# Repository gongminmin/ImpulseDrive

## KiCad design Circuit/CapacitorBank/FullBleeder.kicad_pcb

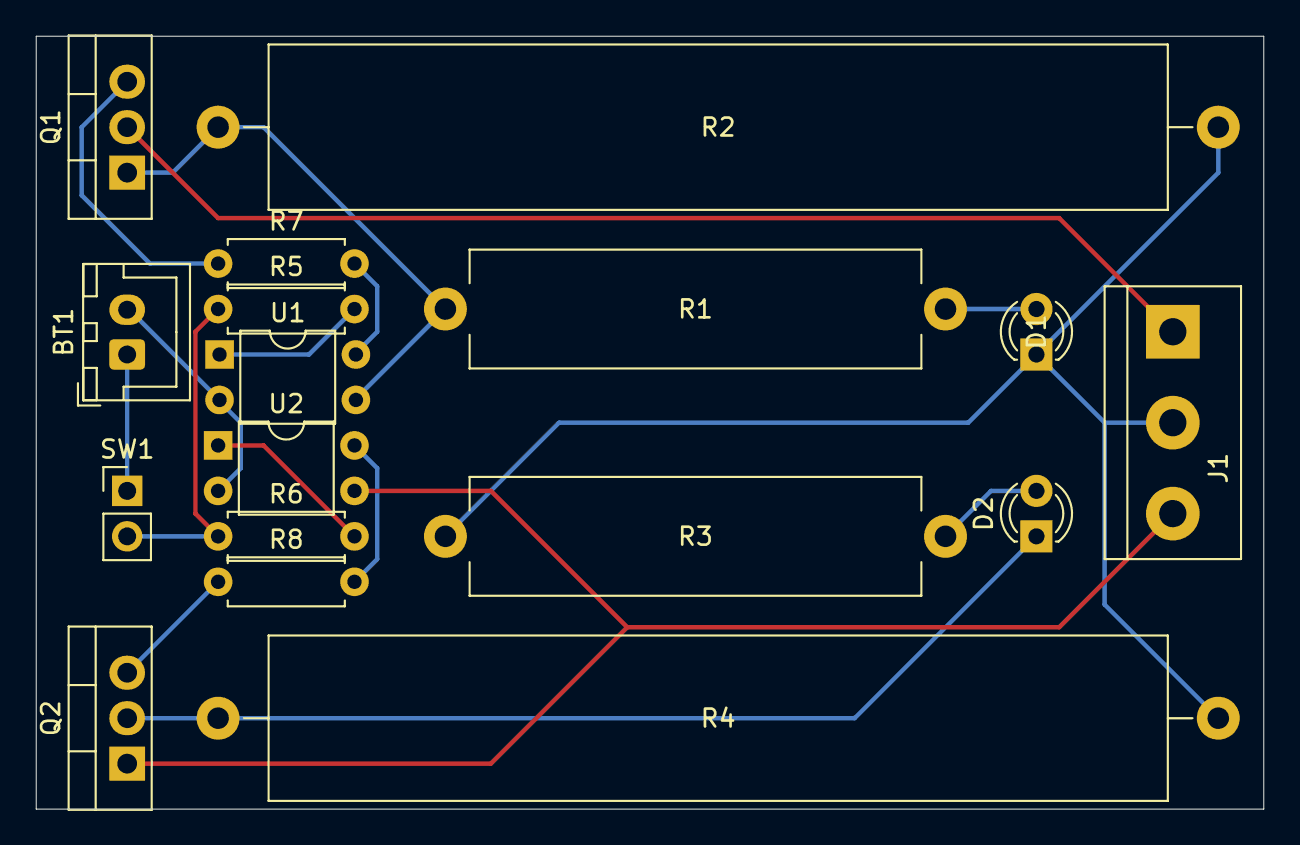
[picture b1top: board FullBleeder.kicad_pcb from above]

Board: 2 copper layers, 68.6 x 43.2 mm, 17 parts (0 on the bottom side), 16 nets.

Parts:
BT1: 12V Battery; JST_XH_B2B-XH-A_1x02_P2.50mm_Vertical
D1, D2: LED; LED_D3.0mm_FlatTop
J1: Power; TerminalBlock_bornier-3_P5.08mm
Q1, Q2: BT138-800; TO-220-3_Vertical
R1, R3: 43K/5W; R_Axial_Power_L25.0mm_W6.4mm_P27.94mm
R2, R4: 20K/10W; R_Axial_Power_L50.0mm_W9.0mm_P55.88mm
R5, R6: 1K; R_Axial_DIN0207_L6.3mm_D2.5mm_P7.62mm_Horizontal
R7, R8: 10K; R_Axial_DIN0207_L6.3mm_D2.5mm_P7.62mm_Horizontal
SW1: SW_Push; PinHeader_1x02_P2.54mm_Vertical
U1, U2: PC817; DIP-4_W7.62mm

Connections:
/CapacitorCenter: D1.1, J1.2, R2.2, R3.1, R4.1
/CapacitorPower+: J1.1, Q1.2
/CapacitorPower-: J1.3, Q2.1, U2.3
unnamed: BT1.1, SW1.1
unnamed: BT1.2, U1.2, U2.2
unnamed: D1.2, R1.2
unnamed: D2.1, Q2.2, R4.2
unnamed: D2.2, R3.2
unnamed: Q1.1, R1.1, R2.1, U1.3
unnamed: Q1.3, R7.1
unnamed: Q2.3, R8.1
unnamed: R5.1, R6.1, SW1.2
unnamed: R5.2, U1.1
unnamed: R6.2, U2.1
unnamed: R7.2, U1.4
unnamed: R8.2, U2.4

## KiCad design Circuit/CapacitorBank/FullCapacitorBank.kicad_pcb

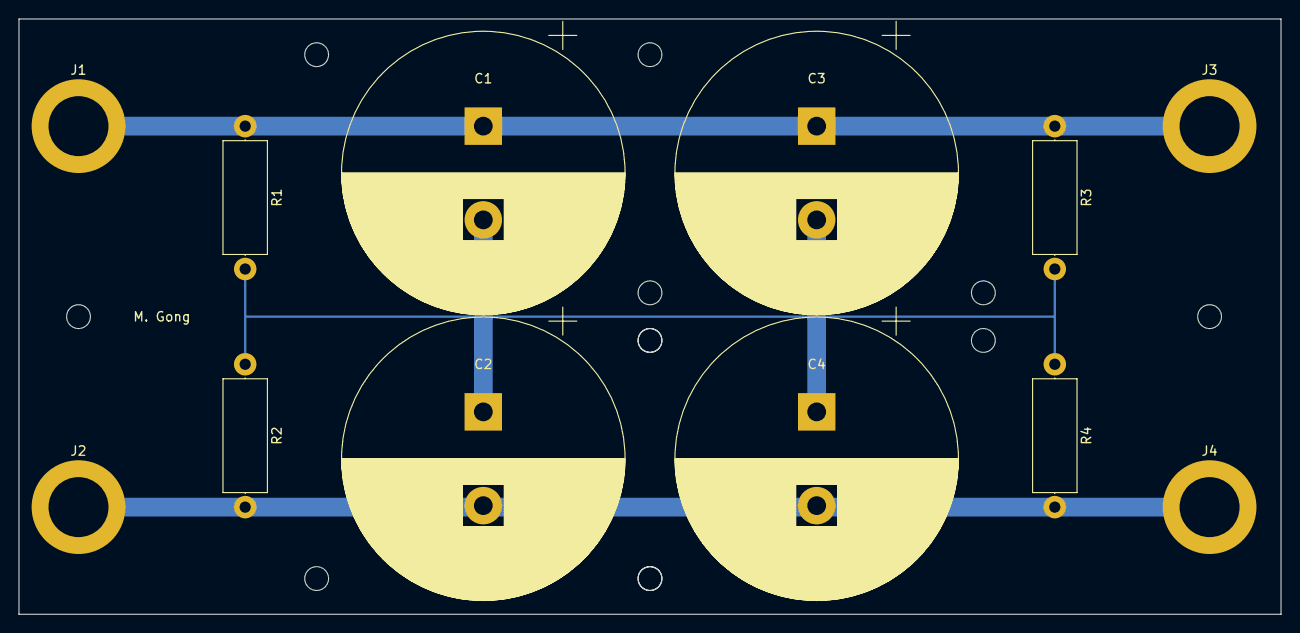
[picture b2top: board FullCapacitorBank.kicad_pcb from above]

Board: 2 copper layers, 134.6 x 63.5 mm, 12 parts (0 on the bottom side), 3 nets.

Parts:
C1, C2, C3, C4: 330uF/450V; CP_Radial_D30.0mm_P10.00mm_SnapIn
J1: Input+; MountingHole_6.4mm_M6_ISO14580_Pad
J2: Input-; MountingHole_6.4mm_M6_ISO14580_Pad
J3: Output+; MountingHole_6.4mm_M6_ISO14580_Pad
J4: Output-; MountingHole_6.4mm_M6_ISO14580_Pad
R1, R2, R3, R4: 220K 5W; R_Axial_DIN0414_L11.9mm_D4.5mm_P15.24mm_Horizontal

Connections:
/Power+: C1.1, C3.1, J1.1, J3.1, R1.1, R3.1
/Power-: C2.2, C4.2, J2.1, J4.1, R2.2, R4.2
unnamed: C1.2, C2.1, C3.2, C4.1, R1.2, R2.1, R3.2, R4.1

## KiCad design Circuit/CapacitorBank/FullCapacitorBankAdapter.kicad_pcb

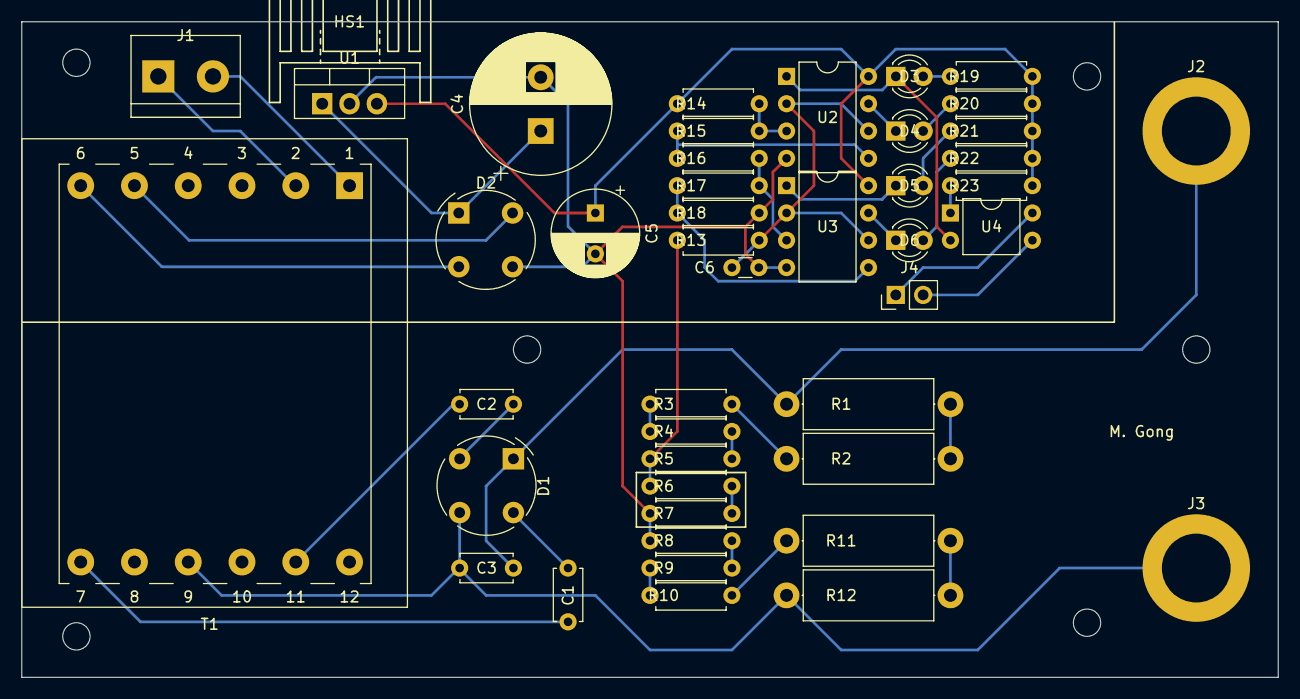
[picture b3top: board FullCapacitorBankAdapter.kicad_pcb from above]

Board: 2 copper layers, 116.8 x 61.0 mm, 45 parts (0 on the bottom side), 39 nets.

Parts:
C1, C2, C3: 1nF/1kV; C_Disc_D4.7mm_W2.5mm_P5.00mm
C4: 2200uF; CP_Radial_D13.0mm_P5.00mm
C5: 0.1uF; CP_Radial_D8.0mm_P3.80mm
C6: 0.1uF; C_Disc_D3.0mm_W1.6mm_P2.50mm
D1, D2: 2W10; Diode_Bridge_Round_D9.0mm
D3, D4, D5, D6: LED; LED_D3.0mm_FlatTop
HS1: Heatsink; Heatsink_TO220_15x10mm
J1: AC Power In; TerminalBlock_bornier-2_P5.08mm
J2: Output+; MountingHole_6.4mm_M6_ISO14580_Pad
J3: Output-; MountingHole_6.4mm_M6_ISO14580_Pad
J4: To Control; PinHeader_1x02_P2.54mm_Vertical
R1, R2, R11, R12: 1M 1W; R_Axial_DIN0414_L11.9mm_D4.5mm_P15.24mm_Horizontal
R3, R10: 300K; R_Axial_DIN0207_L6.3mm_D2.5mm_P7.62mm_Horizontal
R4, R5, R8, R9: 220K; R_Axial_DIN0207_L6.3mm_D2.5mm_P7.62mm_Horizontal
R6, R7, R14: 20K; R_Axial_DIN0207_L6.3mm_D2.5mm_P7.62mm_Horizontal
R13, R23: 1K; R_Axial_DIN0207_L6.3mm_D2.5mm_P7.62mm_Horizontal
R15, R16, R17, R18: 4.7K; R_Axial_DIN0207_L6.3mm_D2.5mm_P7.62mm_Horizontal
R19, R20, R21, R22: 2.2K; R_Axial_DIN0207_L6.3mm_D2.5mm_P7.62mm_Horizontal
T1: 6:6:33+33; Transformer_Generic_EE42_12Pin
U1: L7812; TO-220-3_Vertical
U2, U3: LM393; DIP-8_W7.62mm
U4: PC817; DIP-4_W7.62mm

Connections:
+12V: C5.1, R14.2, R19.1, R20.1, R21.1, R22.1, R23.2, U1.3, U2.8, U3.8
/ControlGND: J4.2, U4.3
/ControlSignal: J4.1, U4.4
/PowerIn+: J1.2, T1.1
/PowerIn-: J1.1, T1.2
/PowerOut+: C3.1, D1.1, J2.1, R1.1
/PowerOut-: C3.2, D1.3, J3.1, R12.2, T1.9
GND: C4.2, C5.2, C6.2, D2.3, R7.2, R8.1, R18.1, U1.2, U2.4, U3.4
unnamed: C1.1, D1.4
unnamed: C1.2, T1.7
unnamed: C2.1, D1.2
unnamed: C2.2, T1.11
unnamed: C4.1, D2.1, U1.1
unnamed: C6.1, R13.1, U2.2, U2.6, U3.2, U3.6
unnamed: D2.2, T1.6
unnamed: D2.4, T1.5
unnamed: D3.1, U2.1, U4.2
unnamed: D3.2, R19.2
unnamed: D4.1, U2.7
unnamed: D4.2, R20.2
unnamed: D5.1, U3.1
unnamed: D5.2, R21.2
unnamed: D6.1, U3.7
unnamed: D6.2, R22.2
unnamed: R1.2, R2.1
unnamed: R2.2, R3.1
unnamed: R3.2, R4.1
unnamed: R4.2, R5.1
unnamed: R6.2, R7.1
unnamed: R8.2, R9.1
unnamed: R9.2, R10.1
unnamed: R10.2, R11.1
unnamed: R11.2, R12.1
unnamed: R5.2, R6.1, R13.2
unnamed: R14.1, R15.2, U2.3
unnamed: R15.1, R16.2, U2.5
unnamed: R16.1, R17.2, U3.3
unnamed: R17.1, R18.2, U3.5
unnamed: R23.1, U4.1

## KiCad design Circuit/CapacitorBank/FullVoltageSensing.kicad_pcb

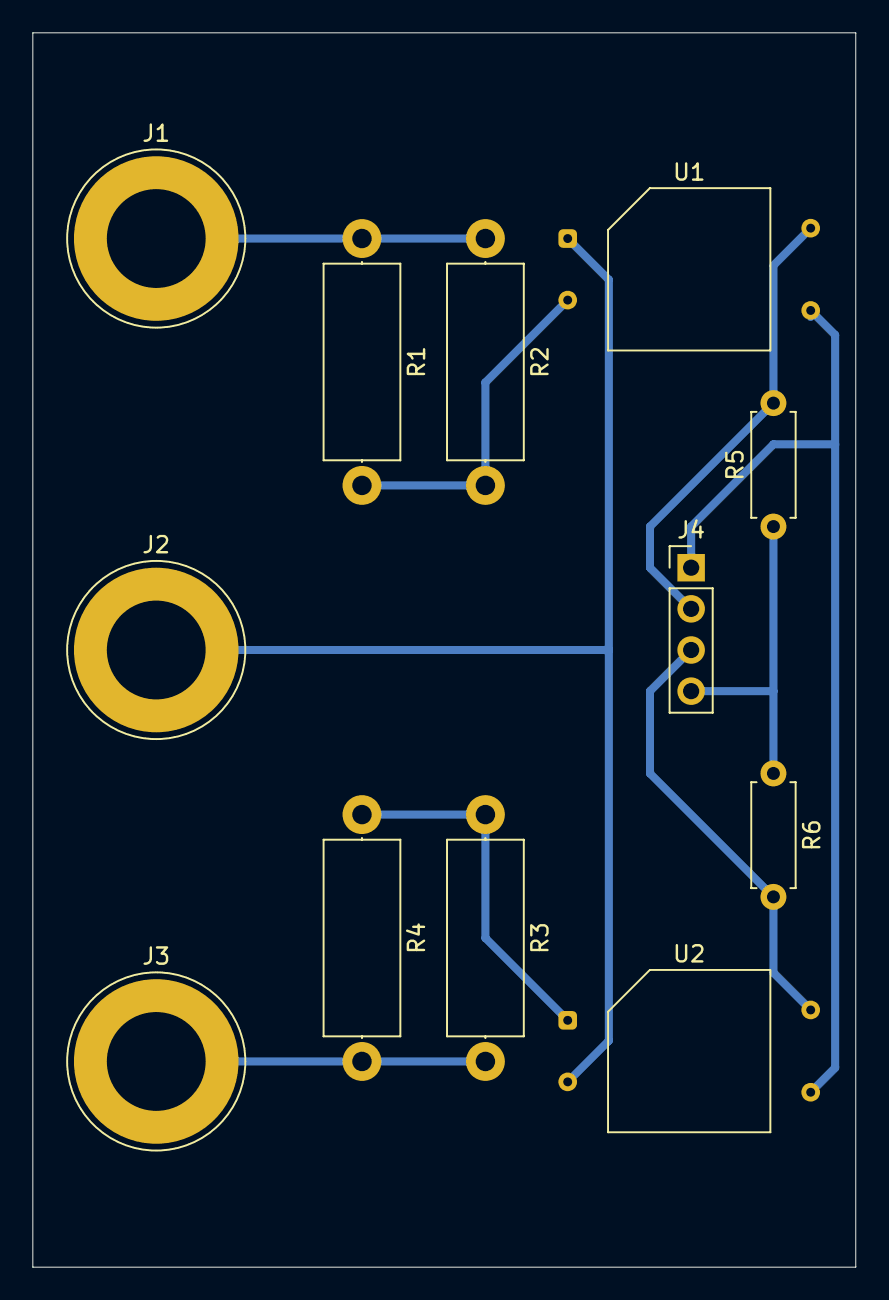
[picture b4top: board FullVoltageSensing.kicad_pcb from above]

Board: 2 copper layers, 50.8 x 76.2 mm, 12 parts (0 on the bottom side), 9 nets.

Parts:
J1: Output+; Banana_Jack_1Pin
J2: BleederCenter; Banana_Jack_1Pin
J3: Output-; Banana_Jack_1Pin
J4: To Control; PinHeader_1x04_P2.54mm_Vertical
R1, R2, R3, R4: 42K/5W; R_Axial_DIN0414_L11.9mm_D4.5mm_P15.24mm_Horizontal
R5, R6: 4.7K; R_Axial_DIN0207_L6.3mm_D2.5mm_P7.62mm_Horizontal
U1, U2: VTL5C; PerkinElmer_VTL5C

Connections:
/BleederCenter: J2.1, U1.1, U2.2
/ControlPower+: J4.1, U1.4, U2.4
/ControlPower-: J4.4, R5.1, R6.1
/ControlSignal1: J4.2, R5.2, U1.3
/ControlSignal2: J4.3, R6.2, U2.3
/PowerOut+: J1.1, R1.1, R2.1
/PowerOut-: J3.1, R3.2, R4.2
unnamed: R1.2, R2.2, U1.2
unnamed: R3.1, R4.1, U2.1

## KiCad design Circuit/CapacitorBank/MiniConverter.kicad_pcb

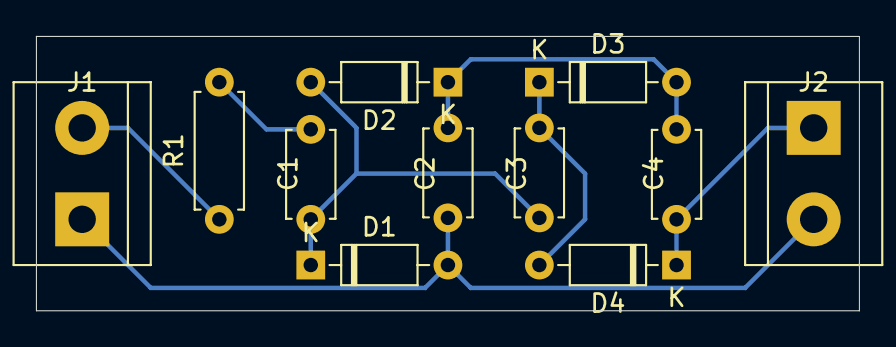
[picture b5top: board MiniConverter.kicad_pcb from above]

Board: 2 copper layers, 45.7 x 15.2 mm, 11 parts (0 on the bottom side), 7 nets.

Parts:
C1, C2, C3, C4: 1nF; C_Disc_D4.7mm_W2.5mm_P5.00mm
D1, D2, D3, D4: 1N4148; D_DO-35_SOD27_P7.62mm_Horizontal
J1: AC Power In; TerminalBlock_bornier-2_P5.08mm
J2: To Capacitors; TerminalBlock_bornier-2_P5.08mm
R1: 220; R_Axial_DIN0207_L6.3mm_D2.5mm_P7.62mm_Horizontal

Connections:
/ACPowerIn+: J1.2, R1.2
/ACPowerIn-: C2.2, D1.2, J1.1, J2.2
/CapacitorPower+: C4.1, D4.1, J2.1
unnamed: C1.1, C3.2, D1.1, D2.2
unnamed: C1.2, R1.1
unnamed: C2.1, C4.2, D2.1, D3.2
unnamed: C3.1, D3.1, D4.2

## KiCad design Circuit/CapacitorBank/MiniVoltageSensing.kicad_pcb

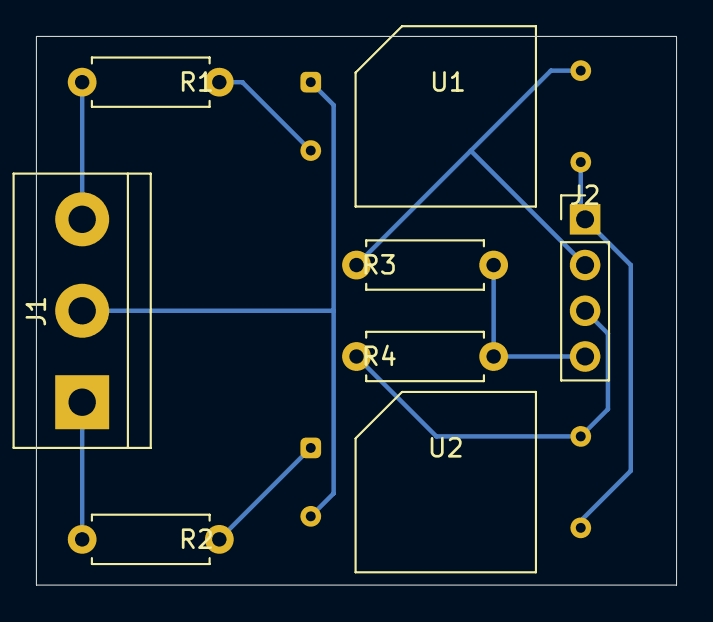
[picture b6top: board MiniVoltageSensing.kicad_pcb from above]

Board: 2 copper layers, 35.6 x 30.5 mm, 8 parts (0 on the bottom side), 9 nets.

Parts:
J1: From Capacitor Bank; TerminalBlock_bornier-3_P5.08mm
J2: To Control; PinHeader_1x04_P2.54mm_Vertical
R1, R2: 4.3K; R_Axial_DIN0207_L6.3mm_D2.5mm_P7.62mm_Horizontal
R3, R4: 4.7K; R_Axial_DIN0207_L6.3mm_D2.5mm_P7.62mm_Horizontal
U1, U2: VTL5C; PerkinElmer_VTL5C

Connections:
/BleederCenter: J1.2, U1.1, U2.2
/ControlPower+: J2.1, U1.4, U2.4
/ControlPower-: J2.4, R3.1, R4.1
/ControlSignal1: J2.2, R3.2, U1.3
/ControlSignal2: J2.3, R4.2, U2.3
/PowerOut+: J1.3, R1.1
/PowerOut-: J1.1, R2.1
unnamed: R1.2, U1.2
unnamed: R2.2, U2.1

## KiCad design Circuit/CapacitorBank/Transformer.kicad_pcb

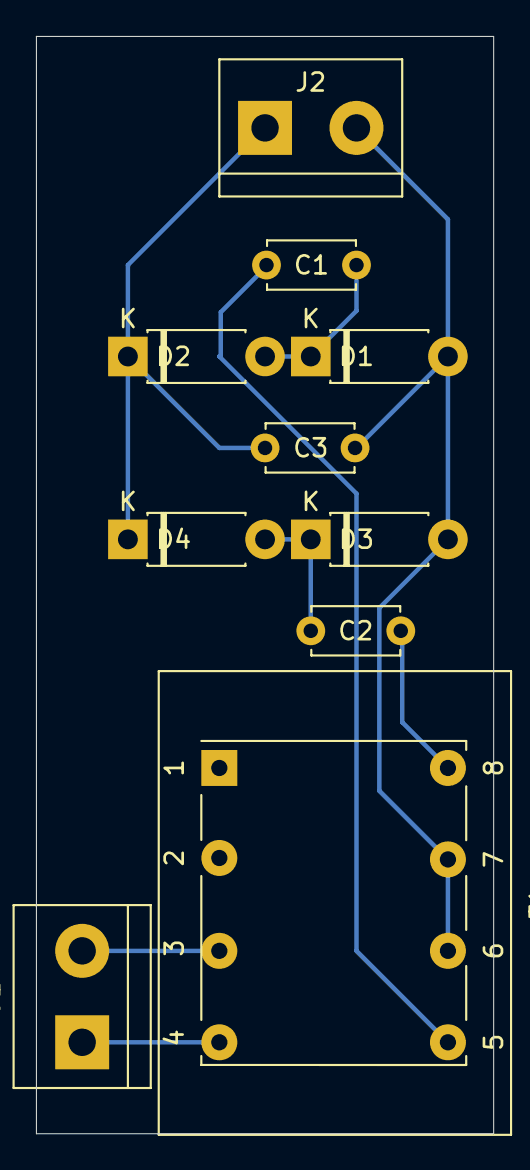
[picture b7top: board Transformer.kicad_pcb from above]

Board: 2 copper layers, 25.4 x 61.0 mm, 10 parts (0 on the bottom side), 8 nets.

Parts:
C1, C2, C3: 1nF; C_Disc_D4.7mm_W2.5mm_P5.00mm
D1, D2, D3, D4: 1N4007; D_DO-41_SOD81_P7.62mm_Horizontal
J1: AC Power In; TerminalBlock_bornier-2_P5.08mm
J2: To Capacitors; TerminalBlock_bornier-2_P5.08mm
T1: 6:200; Transformer_Generic_EE25_8Pin

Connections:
/ACPowerIn+: J1.2, T1.3
/ACPowerIn-: J1.1, T1.4
/CapacitorPower+: C3.1, D2.1, D4.1, J2.1
/CapacitorPower-: C3.2, D1.2, D3.2, J2.2, T1.6, T1.7
unnamed: C1.1, D1.1, D2.2
unnamed: C1.2, T1.5
unnamed: C2.1, D3.1, D4.2
unnamed: C2.2, T1.8
